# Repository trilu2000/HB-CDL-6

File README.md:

# HB-CDL-6 
ein Asksin++ basiertes Touch-Codeschloss 

## Features
* Codeschloss mit 6 Kanälen zur direkten Ansteuerung von 2 bis 3 Aktoren
* Klingeltaster zur direkten Ansteuerung von HM-OU-CFM-Pl oder ähnlichen Geräten
* 12 individuelle Pins können bis zu 6 Kanälen zugeornet werden
* Großflächige kapazitive Touchfläche 
* Buzzer bestätigt Tastendruck 
* RGB Hintergrundbeleuchtung zur individuellen Farb- und Helligkeitsanpassung
*  Integration in ein gängiges Schalterprogramm von Gira für den Außenbereich (Gira TX-44)
* Verwalten der PIN's über die CCU Oberfläche
* Stromversorgung ist an die lokalen Gegebenheiten anpassbar (<20 V AC, <20V DC, 5V DC)

Support thread: https://homematic-forum.de/forum/viewtopic.php?f=76&t=62530

## Nutzung

Zuerst muss das Device natürlich mit der CCU verbunden werden. Per Default ist der Klingelknopf auf Kanal 6 geschaltet und braucht natürlich kein Passwort.
Weiter unten in der Maske kann man die PIN's und zugehörigen Channel setzen.

Per Default hat das Gerät den Master PIN '12345678' in Channel 1 auf Slot 0 für alle Schaltkanäle gesetzt.
Testen kann man das wie folgt: Wir wollen Kanal zwei Schalten, dazu drücken wir eine 2 gefolgt vom Masterpasswort und abgeschlossen mit einer #
Jetzt bleibt die Beleuchtung etwas länger hell und abschließend hört ihr den doppelten Quittierungston.

Mein Setup sieht so aus:

| Kanal | Gerät    | Funktion   |
| ----: | :------- | :-----     |
| 1     | Haustür  | öffnen     |
| 2     | Haustür  | verriegeln |
| 3     | Garage   | öffnen     |
| 4     | Garage   | schliessen |
| 5     |          |            |
| 6     | Klingel  | klingeln   |

Meine Frau, meine beiden Söhne und ich haben einen eigenen PIN. Alle diese Pins sind berechtigt für 1, 2, 3 und 4.
Nachdem ich aber zum Schließen der Garage oder Verriegeln der Tür nicht jeweils den langen PIN eingeben möchte und ich das Schadrisiko für gering halte, habe ich einen weiteren PIN '99' angelegt mit der Berechtigung für 2 und 4.

## Steuerungsplatine

Das Platinendesign der Steuerungsplatine basiert auf dem [HMSensor](https://asksinpp.de/Projekte/psi/HMSensor/) Projekt. 
Dort ist auch das Flashen des Bootloaders und setzen der Fuses beschrieben.

Die Spannungsversorgung kann den lokalen Gegebenheiten durch die Bestückung angepasst werden. 
* Bei <20 V AC wird die rechte Wago Klemme bestückt, die zu einem Gleichrichter führt.
* Bei <20 V DC wird die linke Wago Klemme bestückt, die den Gleichrichter umgeht.
* Bei beiden genannten Varianten wird der DC-DC Wandler bestückt.
* Bei 5V DC ist die linke Wago Klemme zu bestücken und der DC-DC Wandler (Lötbrücke Pin1 und Pin3) zu überbrücken.

Ich verwende diesen DC-DC Wandler: https://de.aliexpress.com/item/4000938525410.html

## Touch-Feld

Das Touch-Feld ist relativ einfach gehalten und beinhaltet nur die Touch Flächen der einzelnen Tasten, sowie die Steuerungselektronik auf der Rückseite.

Die Steuerungselektronik ist eine fertige Platine auf Basis des MPR121. Zum direkten Auflöten muß die Platine links und rechts angeschliffen werden, um die Lötaugen zur Hälfte frei zu legen.

Das Modul gibts z.B. hier: https://de.aliexpress.com/item/32821362153.html

## CCU Integration

Die Integration des Geräts ist als Custom Device ausgelegt. Derzeit habe ich die Device-Files manuell in die CCU kopiert, Ziel ist aber das Gerät durch das Installieren von [JP-HB-Devices-addon](https://github.com/jp112sdl/JP-HB-Devices-addon) Verfügungbar zu machen.
Die Files sind derzeit im Github verfügbar (Ich hoffe ich habe alle erwischt, ist schon eine Weile her das ich Raspberrymatic gepatched habe).

## Aufbau

Die Elektronik besteht aus zwei Platinen - der Steuerungsplatine und das Touch-Feld. 
Die weiteren Gehäuseteile (Zwischenrahmen, Platinenabdeckung, Bauteilabdeckung und Klemmrahmen) werden in PLA gedruckt. 
Die sichtbaren Gehäuseteile bestehen aus zwei Aluwinkeln (15x10x2mm, 67mm lang) und zwei Alu-Flach Stücken (15x2mm, 133mm lang), die als Rahmen dienen.

Platinen bestücken, Bootloader aufspielen und Fuses setzen ([HMSensor](https://asksinpp.de/Projekte/psi/HMSensor/)). Es kann auch schon der Sketch aufgespielt werden und die grundsätzliche Funktionalität getestet werden.  

Dann wird die Einheit Touchplatine, Steuerungsplatine und Zwischenrahmen zusammengebaut. Der Zwischenrahmen hält per Klemmung an den WS2812 RGB LEDS der Steuerplatine, alternativ kann mit ein paar Tropfen Sekundenkleber nachgeholfen werden. 
Die Touchplatine wird dann von der anderen Seite in die entsprechende Aussparung gesetzt, wobei darauf geachtet werden muss, das die Stiftleiste in die Lochreihe der Steuerungsplatine gefädelt wird.
Die Touchplatine sollte bereits über die Klemmung im Zwischenrahmen halten, alternativ kann auch hier mit ein paar Tropfen Sekundenkleber nachgeholfen werden.

Zwischen Touchplatine und Acrylscheibe wird ein Blatt dickeres Papier gelegt - kann Tonpapier oder auch normales Kopierpapier (evtl doppelt) sein.
Bitte darauf achten das die Schlitze zwischen Hintergrundbeleuchtung und Acrylscheibe nicht verdeckt werden.
Die Acrylscheibe wird von der Seite eingeschoben. 

Jetzt macht es Sinn die Funktion der Einheit zu prüfen, dazu die Platine per USB Serial Adapter anschliessen.
Das Touchpad sollte initialisiert werden und die WS2812 LEDs leuchten. Auch sollte das Touchpad auf Berührung reagieren, angezeigt durch helleres Leuchten der Hintergrundbeleuchtung und durch einen kurzen Ton des Buzzers.

Nach dem Funktionstest können die Aluwinkel montiert werden. Zum Verleben habe ich etwas grauen Silikon genutzt, es sollte aber auch jeder andere Kleber funtionieren.
Ich habe eine dünne Schicht Silikon auf beide Seiten (kurze komplett, lange nur bis etwa zur Hälfte) des Winkels aufgetragen, beide Winkel aufgesetzt und mit der Monagehilfe1 zum Aushärten fixiert.

Danach können die beiden Seitenteile verklebt werden. Testen ob die Seitenteile passen, dann etwas Silikon auf die unteren Hälften des Flachmaterials, an der Toucheinheit ansetzen und mit Montagehilfe2 zum Aushärten fixieren.

Jetzt kann die Platinenabdeckung auf die Toucheinheit aufgesetzt werden und durch Aufdrücken des Klemmrahmens fixiert werden. 
Der Klemmrahmen sollte relativ stramm sitzen, falls nicht macht es Sinn etwas Kleber zu nutzen.

Danach noch die Bauteilabdeckung aufsetzen und in das Fußteil des Gira TX-44 Rahmens einsetzen. Abdeckung des Gira Rahmens montieren und fertig :-)

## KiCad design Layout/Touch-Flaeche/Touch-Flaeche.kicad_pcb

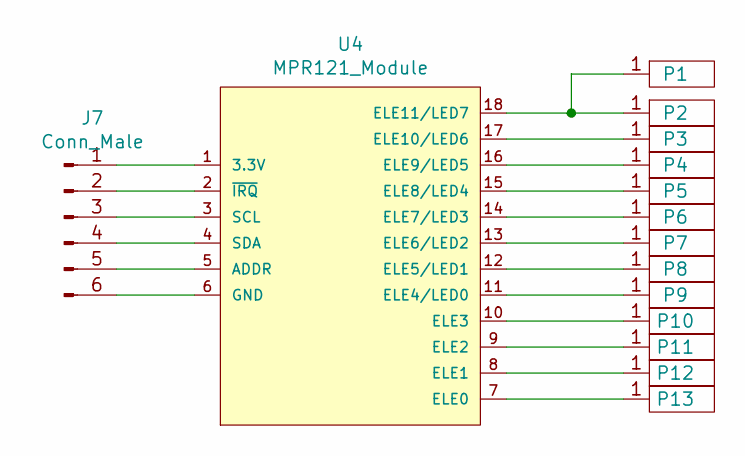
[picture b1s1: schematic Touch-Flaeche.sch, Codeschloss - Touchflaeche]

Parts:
J7: Conn_Male; PinHeader_1x06_P2.00mm_Vertical_SMD_Pin1Left
P1: touchpad_small; touchpad_big
P2, P3, P4, P5, P6, P7, P8, P9, P10, P11, P12, P13: touchpad_small
U4: MPR121_Module; MPR121_SMD

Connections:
unnamed: J7.1, U4.1 (3.3V)
unnamed: J7.2, U4.2 (~IRQ)
unnamed: J7.3, U4.3 (SCL)
unnamed: J7.4, U4.4 (SDA)
unnamed: J7.5, U4.5 (ADDR)
unnamed: J7.6, U4.6 (GND)
unnamed: P1.1, P2.1, U4.18 (ELE11/LED7)
unnamed: P3.1, U4.17 (ELE10/LED6)
unnamed: P4.1, U4.16 (ELE9/LED5)
unnamed: P5.1, U4.15 (ELE8/LED4)
unnamed: P6.1, U4.14 (ELE7/LED3)
unnamed: P7.1, U4.13 (ELE6/LED2)
unnamed: P8.1, U4.12 (ELE5/LED1)
unnamed: P9.1, U4.11 (ELE4/LED0)
unnamed: P10.1, U4.10 (ELE3)
unnamed: P11.1, U4.9 (ELE2)
unnamed: P12.1, U4.8 (ELE1)
unnamed: P13.1, U4.7 (ELE0)

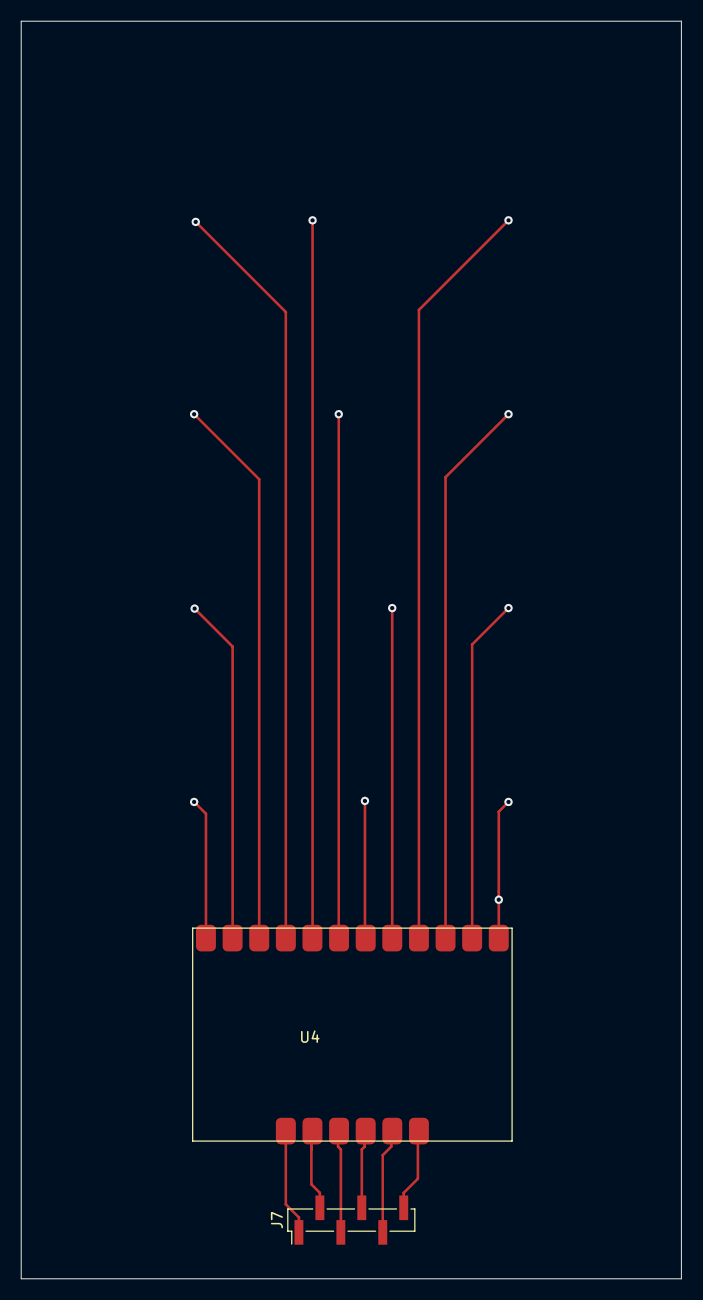
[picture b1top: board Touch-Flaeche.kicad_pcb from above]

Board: 2 copper layers, 63.0 x 120.0 mm, 15 parts (0 on the bottom side), 18 nets.

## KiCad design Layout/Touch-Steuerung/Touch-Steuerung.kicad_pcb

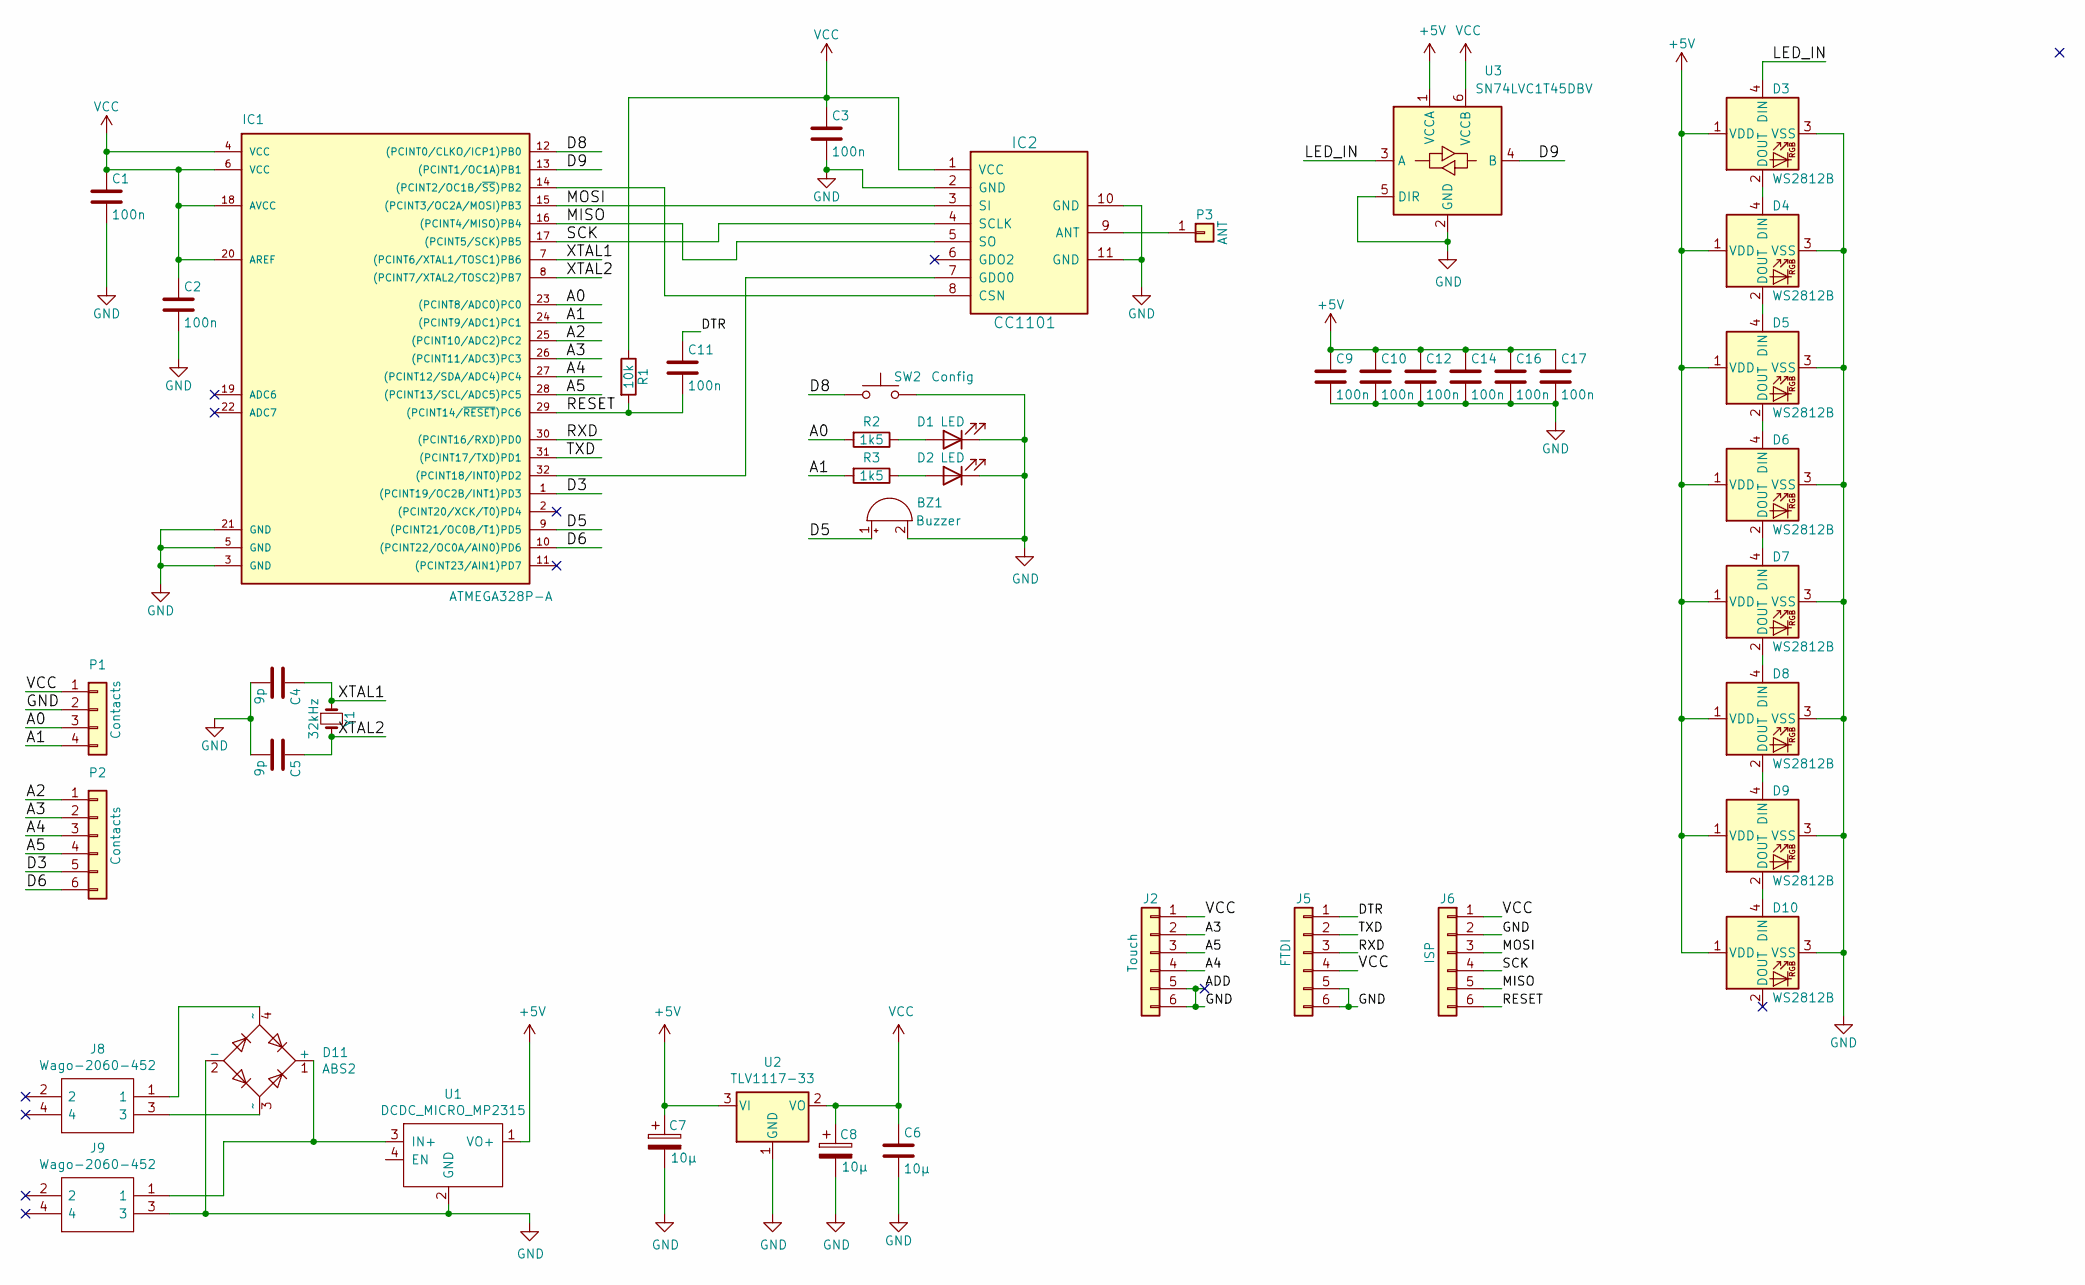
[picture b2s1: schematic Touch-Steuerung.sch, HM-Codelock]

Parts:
BZ1: Buzzer; Buzzer_CUI_CPT-9019S-SMT
C1, C2, C3, C9, C10, C11, C12, C14, C16, C17: 100n; C_0805_2012Metric_Pad1.15x1.40mm_HandSolder
C4, C5: 9p; C_0805_2012Metric_Pad1.15x1.40mm_HandSolder
C6: 10µ; C_0805_2012Metric_Pad1.15x1.40mm_HandSolder
C7, C8: 10µ; CP_Elec_4x5.4
D1, D2: LED; LED_1206_3216Metric_Pad1.42x1.75mm_HandSolder
D3, D4, D5, D6, D7, D8, D9, D10: WS2812B; LED_WS2812B_PLCC4_5.0x5.0mm_P3.2mm
D11: ABS2; Diode_Bridge_Diotec_ABS
IC1: ATMEGA328P-A; TQFP-32_7x7mm_P0.8mm
IC2: CC1101; CC1101_Module
J2: Touch; Pin_Header_Straight_1x06_Pitch2.00mm
J5: FTDI; PinHeader_1x06_P2.54mm_Vertical
J6: ISP; PinHeader_1x06_P2.54mm_Vertical
J8, J9: Wago-2060-452; Manufacturer_Part_Number 2060-452/998-404
P1: Contacts; Pin_Header_Straight_1x04_Pitch2.54mm
P2: Contacts; Pin_Header_Straight_1x06_Pitch2.54mm
P3: ANT; Pin_Header_Straight_1x01_Pitch2.00mm
R1: 10k; R_0805_2012Metric_Pad1.15x1.40mm_HandSolder
R2, R3: 1k5; R_0805_2012Metric_Pad1.15x1.40mm_HandSolder
SW2: Config; SW_SPST_FSMSM
U1: DCDC_MICRO_MP2315; PIN_DCDC_MICRO_MP2315
U2: TLV1117-33; SOT-223
U3: SN74LVC1T45DBV; SOT-23-6
Y1: 32kHz; Crystal_SMD_MicroCrystal_CC7V-T1A-2Pin_3.2x1.5mm_HandSolder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

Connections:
+5V: C7.1, C9.1, C10.1, C12.1, C14.1, C16.1, C17.1, D3.1 (VDD), D4.1 (VDD), D5.1 (VDD), D6.1 (VDD), D7.1 (VDD), D8.1 (VDD), D9.1 (VDD), D10.1 (VDD), U1.1 (VO+), U2.3 (VI), U3.1 (VCCA)
/A0: IC1.23 ((PCINT8/ADC0)PC0), P1.3, R2.2
/A1: IC1.24 ((PCINT9/ADC1)PC1), P1.4, R3.2
/A2: IC1.25 ((PCINT10/ADC2)PC2), P2.1
/A3: IC1.26 ((PCINT11/ADC3)PC3), J2.2, P2.2
/A4: IC1.27 ((PCINT12/SDA/ADC4)PC4), J2.4, P2.3
/A5: IC1.28 ((PCINT13/SCL/ADC5)PC5), J2.3, P2.4
/D3: IC1.1 ((PCINT19/OC2B/INT1)PD3), P2.5
/D5: BZ1.1 (-), IC1.9 ((PCINT21/OC0B/T1)PD5)
/D6: IC1.10 ((PCINT22/OC0A/AIN0)PD6), P2.6
/D8: IC1.12 ((PCINT0/CLKO/ICP1)PB0), SW2.1
/D9: IC1.13 ((PCINT1/OC1A)PB1), U3.4 (B)
/DTR: C11.1, J5.1
/LED_IN: D3.4 (DIN), U3.3 (A)
/MISO: IC1.16 ((PCINT4/MISO)PB4), IC2.5 (SO), J6.5
/MOSI: IC1.15 ((PCINT3/OC2A/MOSI)PB3), IC2.3 (SI), J6.3
/RESET: C11.2, IC1.29 ((PCINT14/~RESET~)PC6), J6.6, R1.2
/RXD: IC1.30 ((PCINT16/RXD)PD0), J5.3
/SCK: IC1.17 ((PCINT5/SCK)PB5), IC2.4 (SCLK), J6.4
/TXD: IC1.31 ((PCINT17/TXD)PD1), J5.2
/XTAL1: C4.1, IC1.7 ((PCINT6/XTAL1/TOSC1)PB6), Y1.1
/XTAL2: C5.1, IC1.8 ((PCINT7/XTAL2/TOSC2)PB7), Y1.2
GND: BZ1.2 (+), C1.2, C2.2, C3.2, C4.2, C5.2, C6.2, C7.2, C8.2, C9.2, C10.2, C12.2, C14.2, C16.2, C17.2, D1.1 (K), D2.1 (K), D3.3 (VSS), D4.3 (VSS), D5.3 (VSS), D6.3 (VSS), D7.3 (VSS), D8.3 (VSS), D9.3 (VSS), D10.3 (VSS), D11.2 (-), IC1.3 (GND), IC1.5 (GND), IC1.21 (GND), IC2.2 (GND), IC2.10 (GND), IC2.11 (GND), J2.5, J2.6, J5.5, J5.6, J6.2, J9.3, P1.2, SW2.2, U1.2 (GND), U2.1 (GND), U3.2 (GND), U3.5 (DIR)
unnamed: D1.2 (A), R2.1
unnamed: D2.2 (A), R3.1
unnamed: D3.2 (DOUT), D4.4 (DIN)
unnamed: D4.2 (DOUT), D5.4 (DIN)
unnamed: D5.2 (DOUT), D6.4 (DIN)
unnamed: D6.2 (DOUT), D7.4 (DIN)
unnamed: D7.2 (DOUT), D8.4 (DIN)
unnamed: D8.2 (DOUT), D9.4 (DIN)
unnamed: D9.2 (DOUT), D10.4 (DIN)
unnamed: D11.1 (+), J9.1, U1.3 (IN+)
unnamed: D11.3 (~~), J8.3
unnamed: D11.4 (~~), J8.1
unnamed: IC1.14 ((PCINT2/OC1B/~SS~)PB2), IC2.8 (CSN)
unnamed: IC1.32 ((PCINT18/INT0)PD2), IC2.7 (GDO0)
unnamed: IC2.9 (ANT), P3.1
VCC: C1.1, C2.1, C3.1, C6.1, C8.1, IC1.4 (VCC), IC1.6 (VCC), IC1.18 (AVCC), IC1.20 (AREF), IC2.1 (VCC), J2.1, J5.4, J6.1, P1.1, R1.1, U2.2 (VO), U3.6 (VCCB)

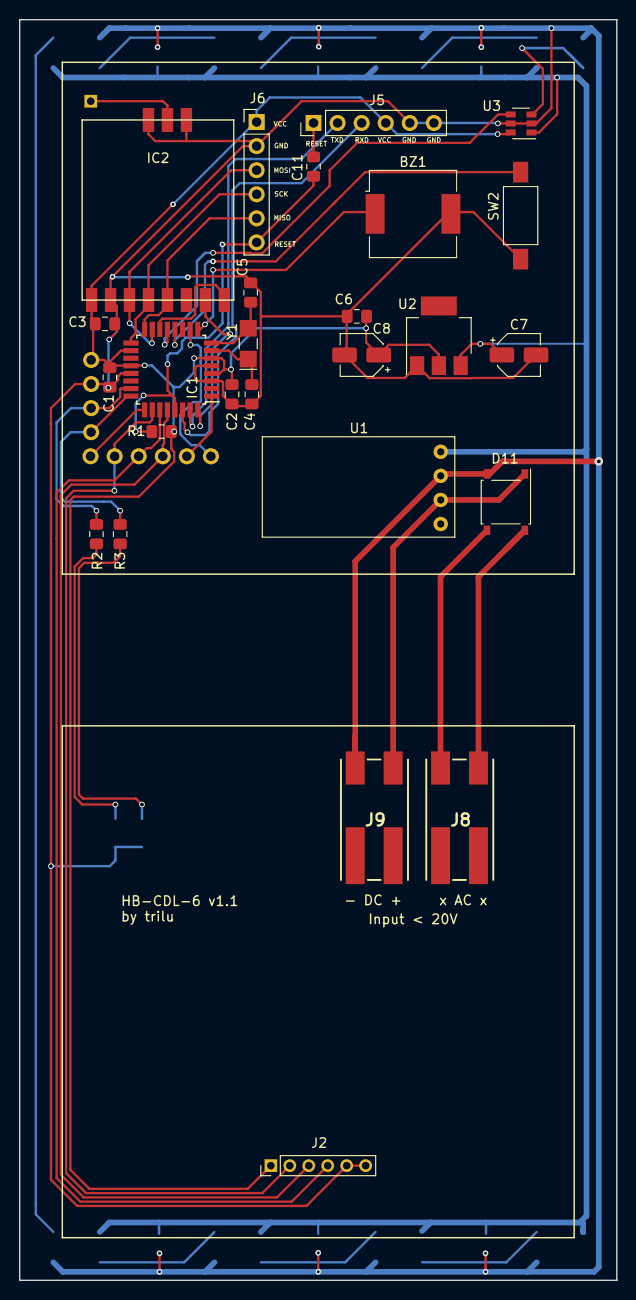
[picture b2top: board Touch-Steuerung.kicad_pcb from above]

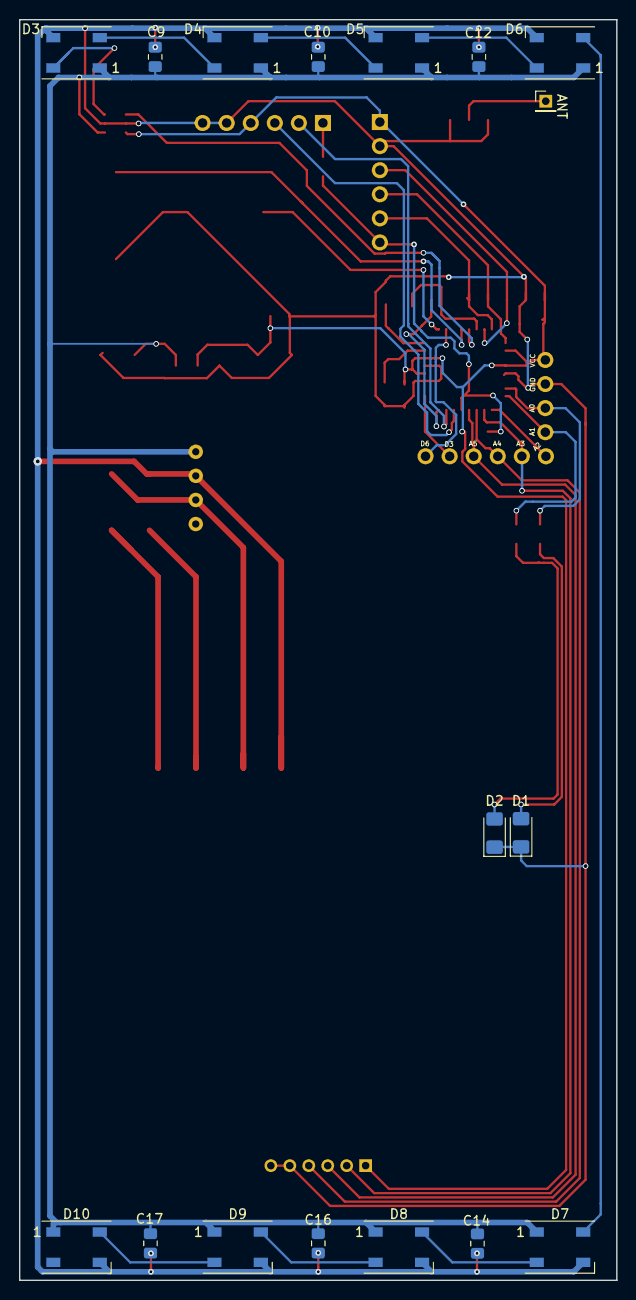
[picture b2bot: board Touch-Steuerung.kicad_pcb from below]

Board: 4 copper layers, 63.0 x 133.0 mm, 45 parts (19 on the bottom side), 39 nets.

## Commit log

2020-11-11 added license
2020-11-12 added support thread

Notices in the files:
README.md:
License: CC BY-NC-SA 4.0
